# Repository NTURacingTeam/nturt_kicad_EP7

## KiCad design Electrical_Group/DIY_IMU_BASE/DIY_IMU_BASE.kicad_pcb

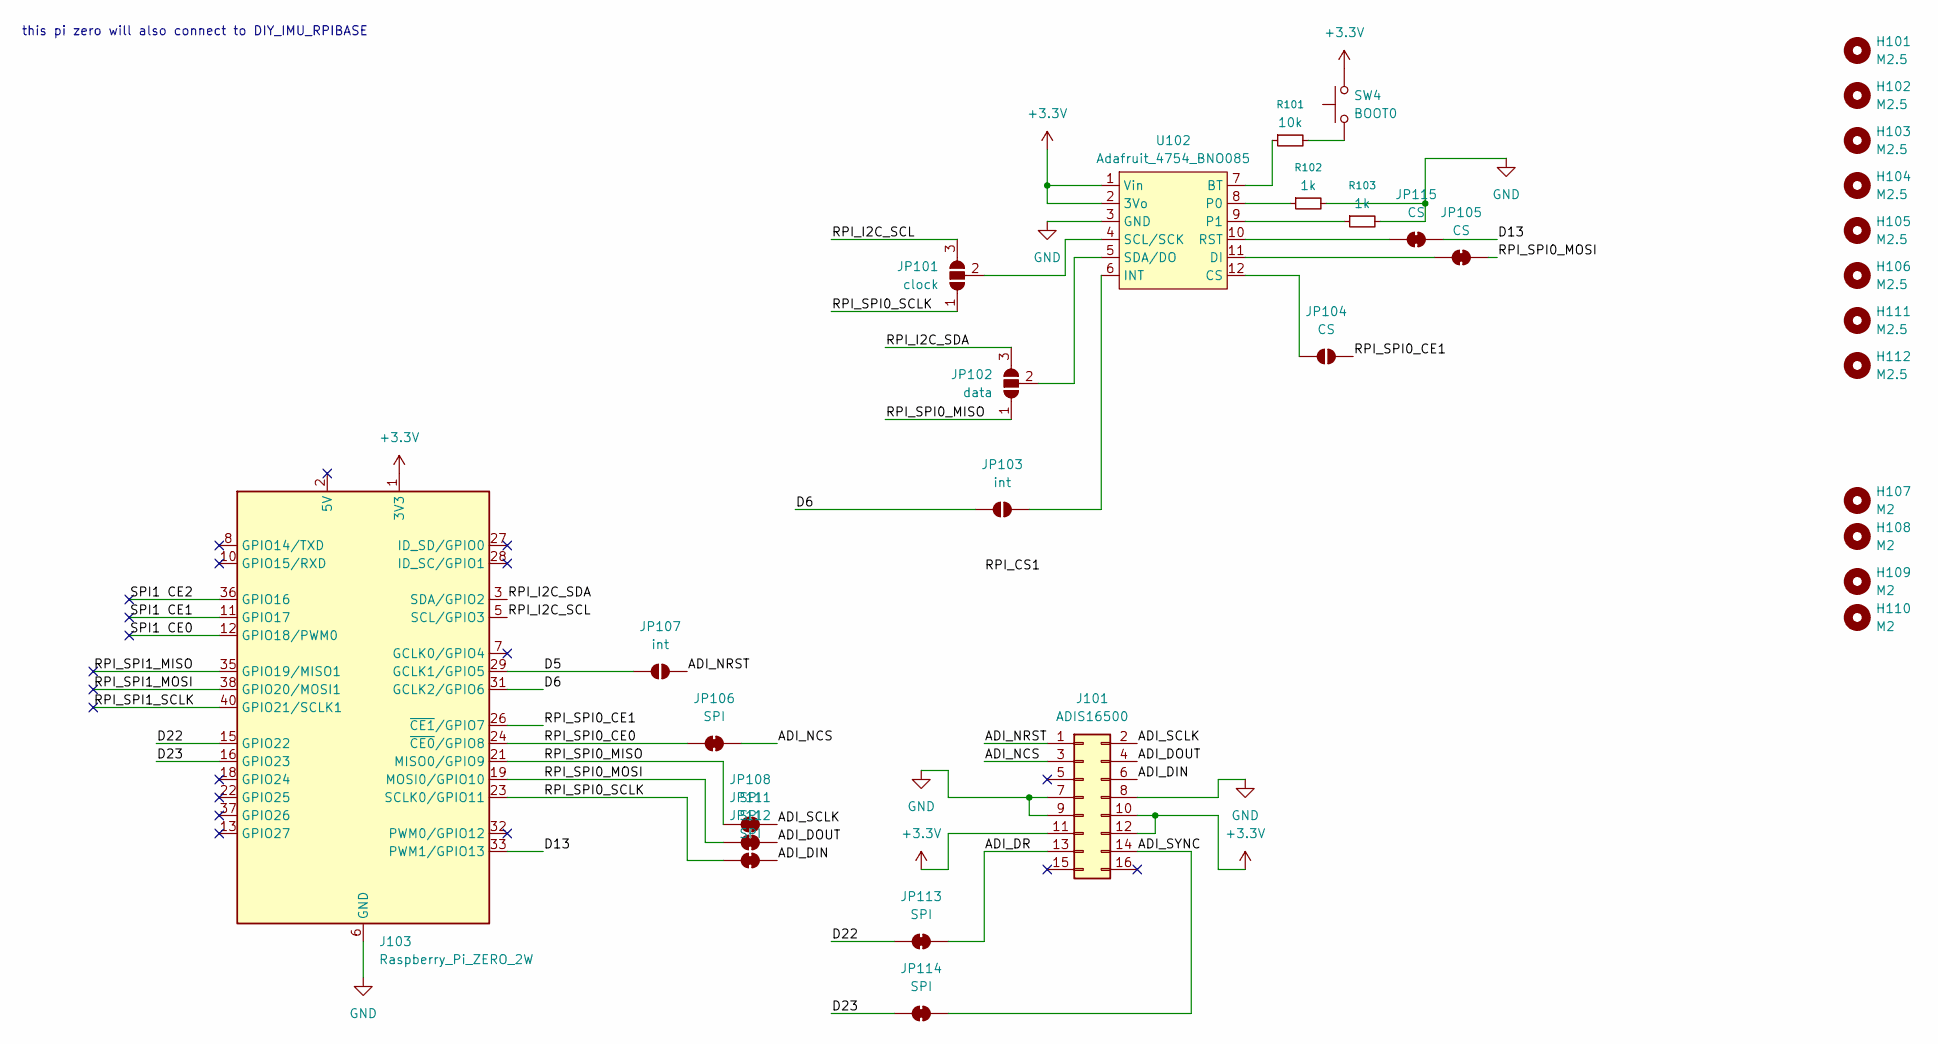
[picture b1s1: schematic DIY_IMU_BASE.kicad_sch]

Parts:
H101, H102, H103, H104, H105, H106, H111, H112: M2.5; MountingHole_2.5mm
H107, H108, H109, H110: M2; MountingHole_2.2mm_M2
J101: ADIS16500; PinHeader_2x08_P2.00mm_Vertical_SMD
J103: Raspberry_Pi_ZERO_2W; PinHeader_2x20_P2.54mm_Vertical
JP101: clock; SolderJumper-3_P1.3mm_Open_RoundedPad1.0x1.5mm
JP102: data; SolderJumper-3_P1.3mm_Open_RoundedPad1.0x1.5mm
JP103, JP107: int; SolderJumper-2_P1.3mm_Open_RoundedPad1.0x1.5mm
JP104: CS; SolderJumper-2_P1.3mm_Open_RoundedPad1.0x1.5mm
JP105, JP115: CS; SolderJumper-2_P1.3mm_Bridged_RoundedPad1.0x1.5mm
JP106, JP108, JP111, JP112, JP113, JP114: SPI; SolderJumper-2_P1.3mm_Bridged_RoundedPad1.0x1.5mm
R101: 10k; R_0805_2012Metric_Pad1.20x1.40mm_HandSolder
R102, R103: 1k; R_0805_2012Metric_Pad1.20x1.40mm_HandSolder
SW4: BOOT0; SW_Tactile_SPST_NO_Straight_CK_PTS636Sx25SMTRLFS
U102: Adafruit_4754_BNO085

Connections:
+3.3V: J101.10, J101.11, J101.12, J103.1 (3V3), J103.17 (3V3), SW4.2, U102.1 (Vin), U102.2 (3Vo)
/ADI_DIN: J101.6, JP112.2 (B)
/ADI_DOUT: J101.4, JP111.2 (B)
/ADI_DR: J101.13, JP113.2 (B)
/ADI_NCS: J101.3, JP106.2 (B)
/ADI_NRST: J101.1, JP107.2 (B)
/ADI_SCLK: J101.2, JP108.2 (B)
/ADI_SYNC: J101.14, JP114.2 (B)
/D5: J103.29 (GCLK1/GPIO5), JP107.1 (A)
/D6: J103.31 (GCLK2/GPIO6), JP103.1 (A)
/D13: J103.33 (PWM1/GPIO13), JP115.2 (B)
/D22: J103.15 (GPIO22), JP113.1 (A)
/D23: J103.16 (GPIO23), JP114.1 (A)
/RPI_I2C_SCL: J103.5 (SCL/GPIO3), JP101.3 (B)
/RPI_I2C_SDA: J103.3 (SDA/GPIO2), JP102.3 (B)
/RPI_SPI0_CE0: J103.24 (~CE0/GPIO8), JP106.1 (A)
/RPI_SPI0_CE1: J103.26 (~CE1/GPIO7), JP104.2 (B)
/RPI_SPI0_MISO: J103.21 (MISO0/GPIO9), JP102.1 (A), JP108.1 (A)
/RPI_SPI0_MOSI: J103.19 (MOSI0/GPIO10), JP105.2 (B), JP111.1 (A)
/RPI_SPI0_SCLK: J103.23 (SCLK0/GPIO11), JP101.1 (A), JP112.1 (A)
/RPI_SPI1_MISO: J103.35 (GPIO19/MISO1)
/RPI_SPI1_MOSI: J103.38 (GPIO20/MOSI1)
/RPI_SPI1_SCLK: J103.40 (GPIO21/SCLK1)
/SPI1 CE0: J103.12 (GPIO18/PWM0)
/SPI1 CE1: J103.11 (GPIO17)
/SPI1 CE2: J103.36 (GPIO16)
GND: J101.7, J101.8, J101.9, J103.6 (GND), J103.9 (GND), J103.14 (GND), J103.20 (GND), J103.25 (GND), J103.30 (GND), J103.34 (GND), J103.39 (GND), R102.2, R103.2, U102.3 (GND)
unnamed: JP101.2 (C), U102.4 (SCL/SCK)
unnamed: JP102.2 (C), U102.5 (SDA/DO)
unnamed: JP103.2 (B), U102.6 (INT)
unnamed: JP104.1 (A), U102.12 (CS)
unnamed: JP105.1 (A), U102.11 (DI)
unnamed: JP115.1 (A), U102.10 (RST)
unnamed: R101.2, SW4.1
unnamed: R101.1, U102.7 (BT)
unnamed: R102.1, U102.8 (P0)
unnamed: R103.1, U102.9 (P1)

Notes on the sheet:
this pi zero will also connect to DIY_IMU_RPIBASE

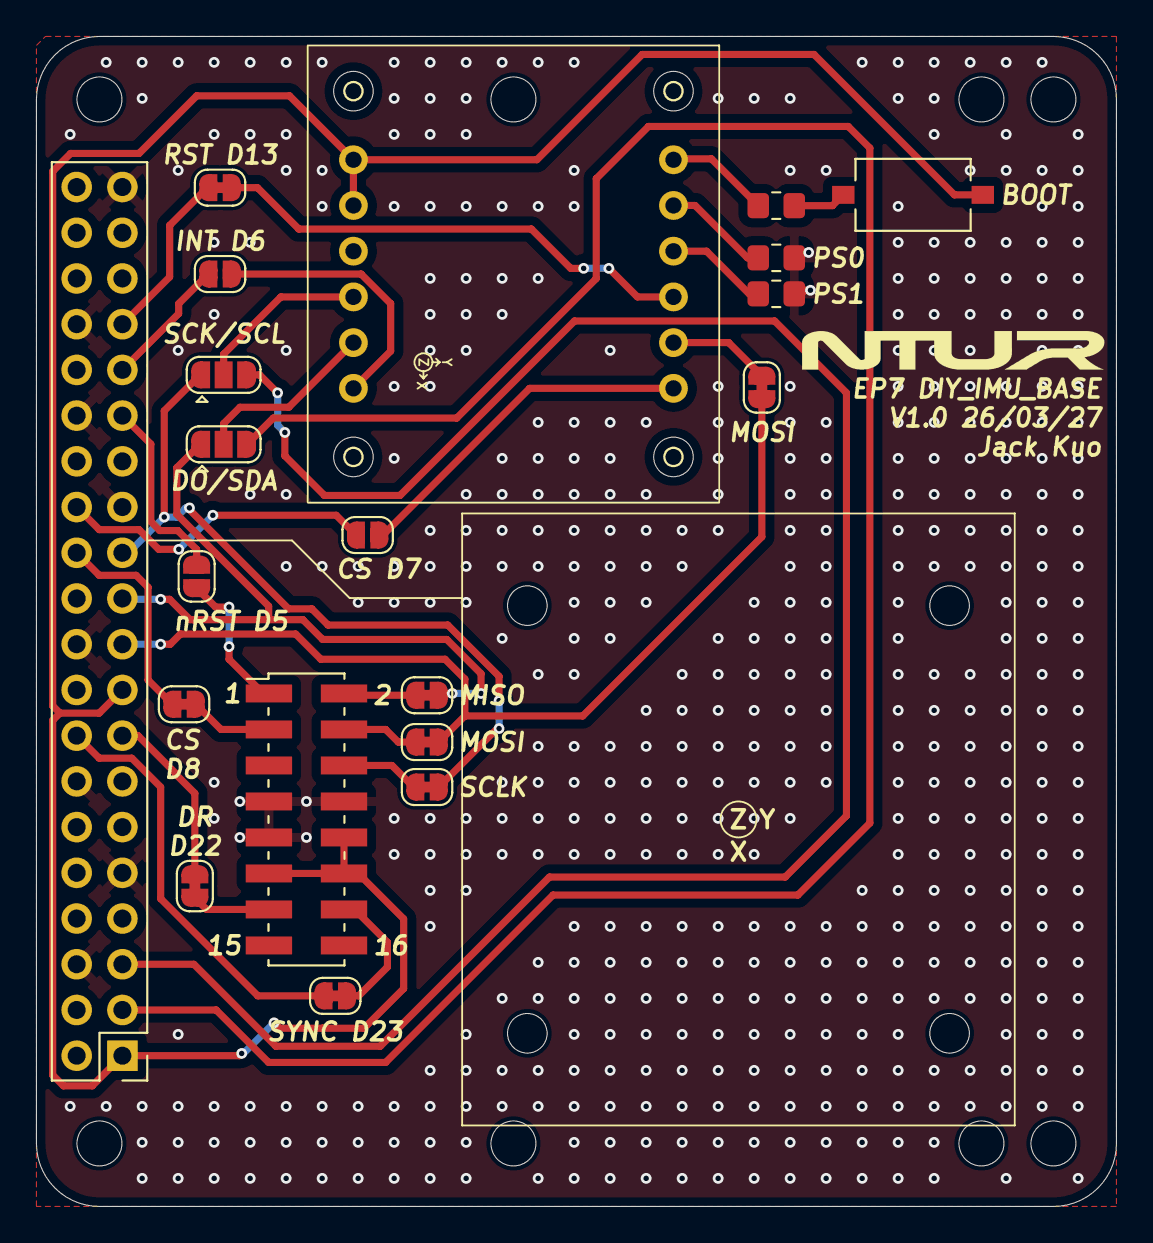
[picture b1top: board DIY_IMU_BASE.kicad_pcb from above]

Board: 2 copper layers, 60.0 x 65.0 mm, 32 parts (0 on the bottom side), 31 nets.

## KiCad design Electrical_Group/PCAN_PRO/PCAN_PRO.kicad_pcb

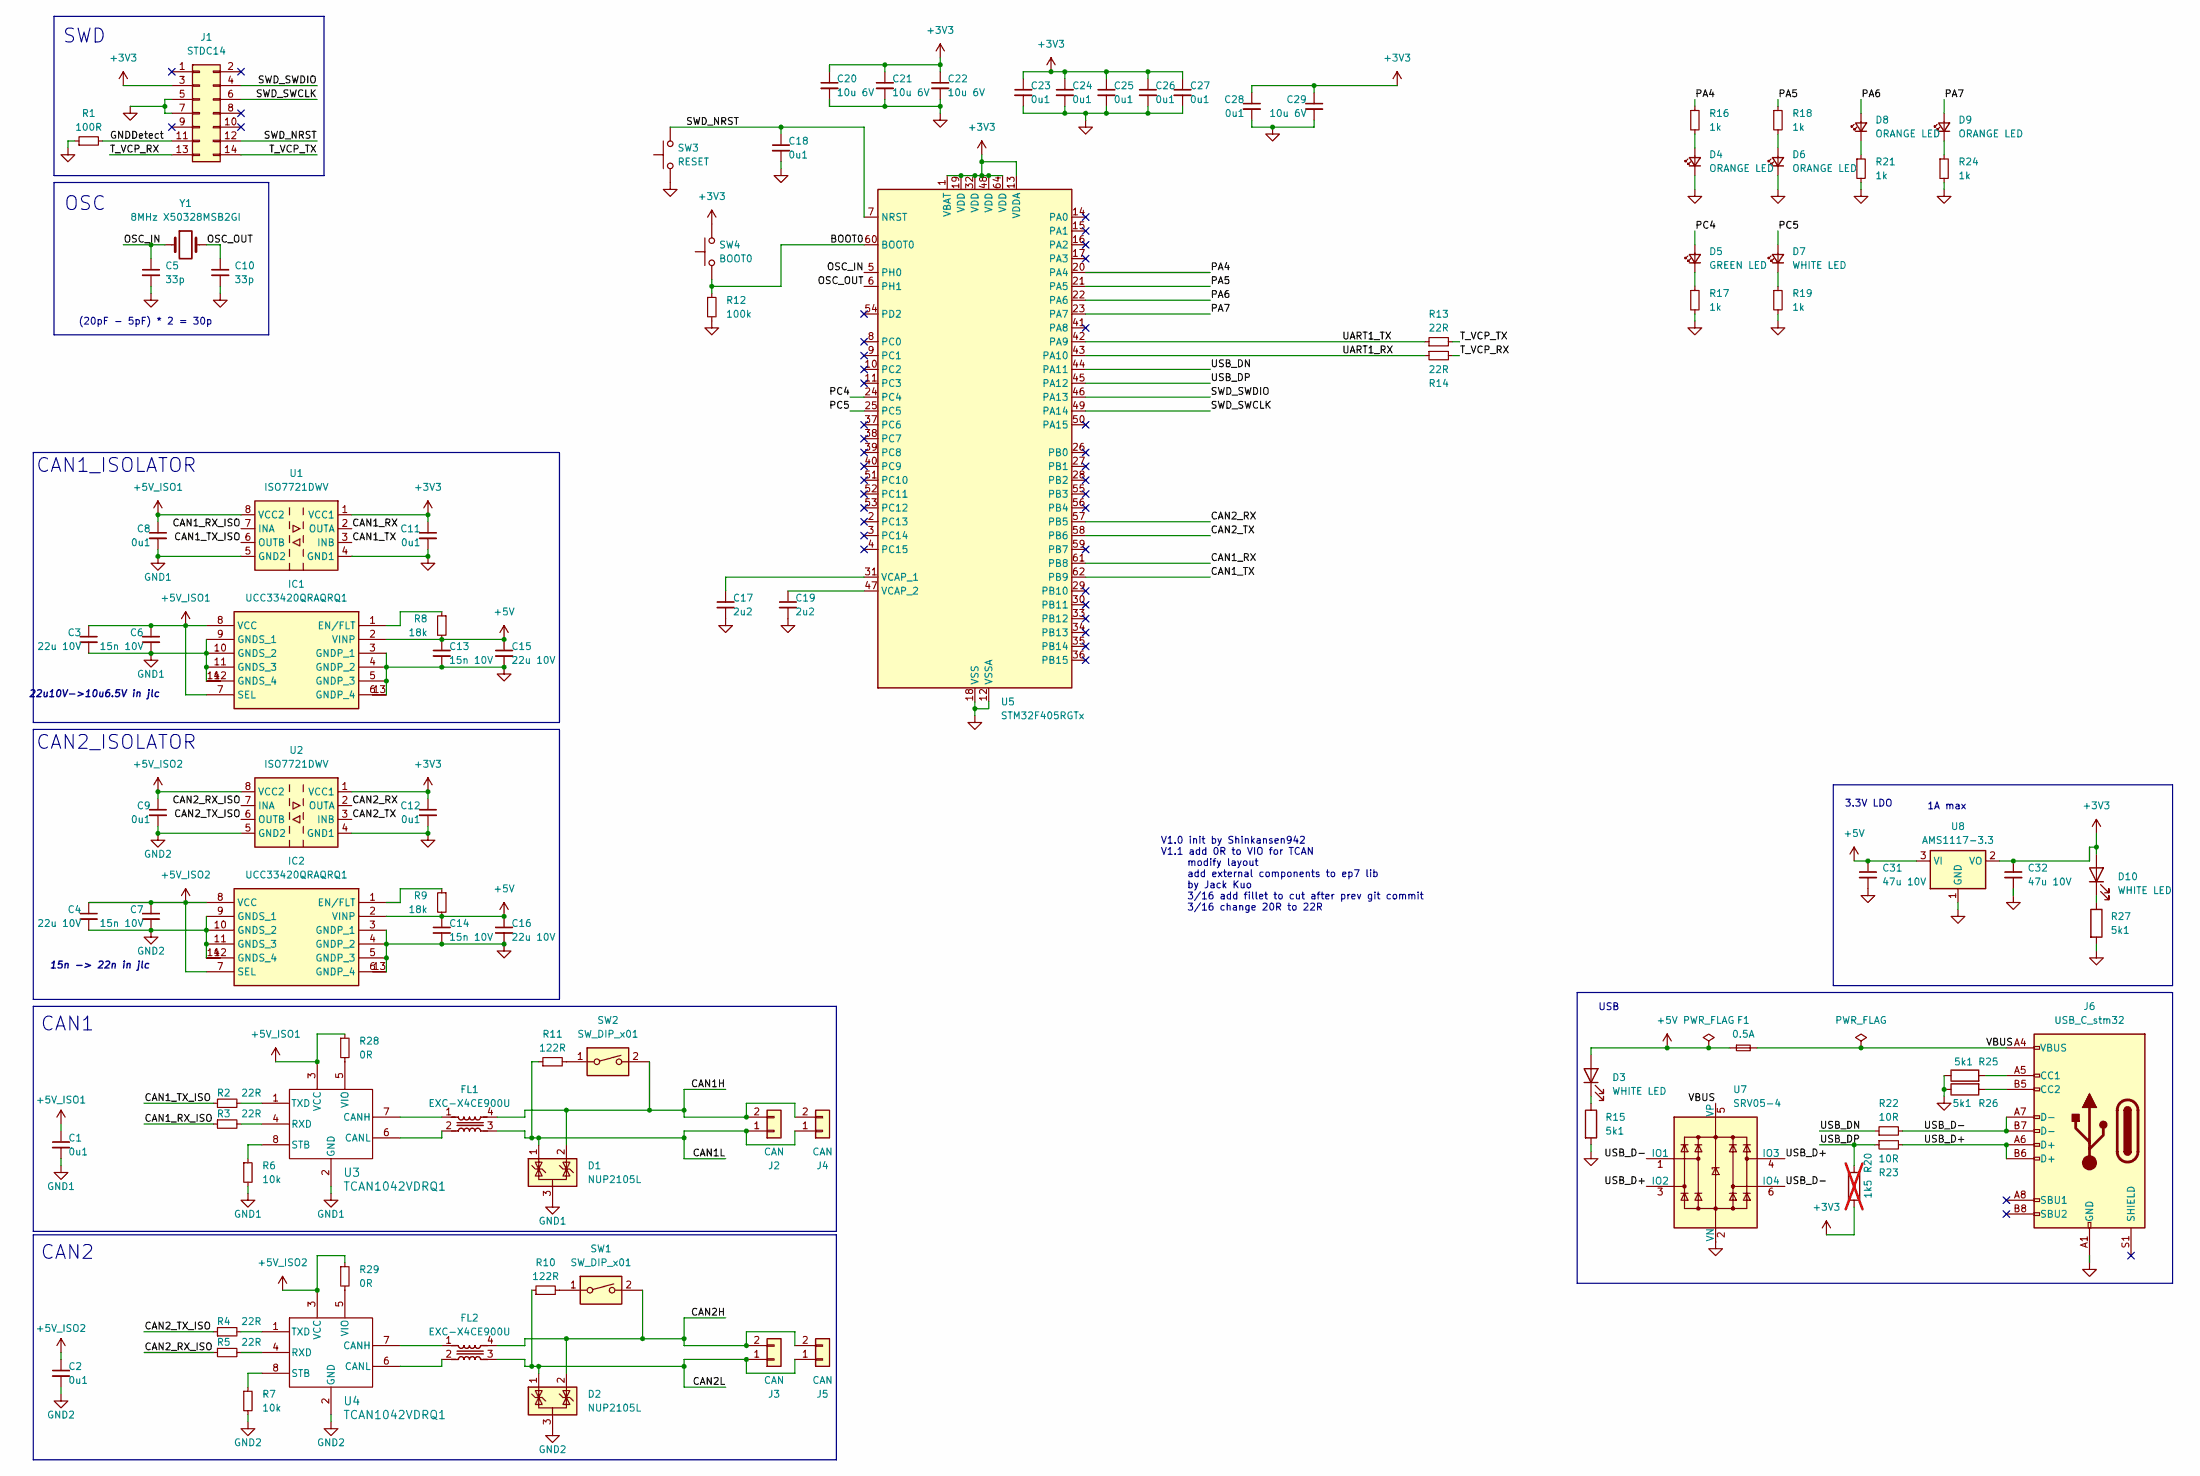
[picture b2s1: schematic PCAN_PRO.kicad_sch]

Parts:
C1, C2, C8, C9, C11, C12, C18, C23, C24, C25, C26, C27, C28: 0u1; C_0402_1005Metric
C3, C4, C15, C16: 22u 10V; C_0402_1005Metric
C5, C10: 33p; C_0402_1005Metric
C6, C7, C13, C14: 15n 10V; C_0402_1005Metric
C17, C19: 2u2; C_0402_1005Metric
C20, C21, C22, C29: 10u 6V; C_0402_1005Metric
C31, C32: 47u 10V; C_1206_3216Metric
D1, D2: NUP2105L; SOT-23
D3, D7, D10: WHITE LED; LED_0603_1608Metric
D4, D6, D8, D9: ORANGE LED; LED_0603_1608Metric
D5: GREEN LED; LED_0603_1608Metric
F1: 0.5A; Fuse_1206_3216Metric
FL1, FL2: EXC-X4CE900U; EXCX4CE900U; Mouser Part Number 667-EXC-X4CE900U
IC1, IC2: UCC33420QRAQRQ1; UCC33020; Mouser Part Number 595-UCC33420QRAQRQ1
J1: STDC14; box_header_14P_pitch1.27
J2, J3, J4, J5: CAN; JST_XH_B2B-XH-A_1x02_P2.50mm_Vertical
J6: USB_C_stm32; USB_C_Receptacle_GCT_USB4105-xx-A_16P_TopMnt_Horizontal
R1: 100R; R_0402_1005Metric
R2, R3, R4, R5, R13, R14: 22R; R_0402_1005Metric
R6, R7: 10k; R_0402_1005Metric
R8, R9: 18k; R_0402_1005Metric
R10, R11: 122R; R_0805_2012Metric
R12: 100k; R_0402_1005Metric
R15, R25, R26, R27: 5k1; R_0402_1005Metric
R16, R17, R18, R19, R21, R24: 1k; R_0402_1005Metric
R20: 1k5; R_0402_1005Metric; not fitted
R22, R23: 10R; R_0402_1005Metric
R28, R29: 0R; R_0402_1005Metric
SW1, SW2: SW_DIP_x01; SW_DIP_SPSTx01_Slide_9.78x4.72mm_W7.62mm_P2.54mm
SW3: RESET; SW_Tactile_SPST_NO_Straight_CK_PTS636Sx25SMTRLFS
SW4: BOOT0; SW_Tactile_SPST_NO_Straight_CK_PTS636Sx25SMTRLFS
U1, U2: ISO7721DWV; SOIC-8_7.5x5.85mm_P1.27mm
U3, U4: TCAN1042VDRQ1; SOIC-8_3.9x4.9mm_P1.27mm
U5: STM32F405RGTx; LQFP-64_10x10mm_P0.5mm
U7: SRV05-4; SOT-23-6
U8: AMS1117-3.3; SOT-223-3_TabPin2
Y1: 8MHz X50328MSB2GI; Crystal_SMD_5032-2Pin_5.0x3.2mm

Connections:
+3V3: C11.1, C12.1, C20.1, C21.1, C22.1, C23.1, C24.1, C25.1, C26.1, C27.1, C28.1, C29.1, C32.1, D10.2 (A), J1.3, R20.1, SW4.2, U1.1 (VCC1), U2.1 (VCC1), U5.1 (VBAT), U5.13 (VDDA), U5.19 (VDD), U5.32 (VDD), U5.48 (VDD), U5.64 (VDD), U8.2 (VO)
+5V: C13.1, C14.1, C15.1, C16.1, C31.1, D3.2 (A), F1.1, IC1.2 (VINP), IC2.2 (VINP), R8.2, R9.2, U8.3 (VI)
+5V_ISO1: C1.1, C3.1, C6.1, C8.1, IC1.7 (SEL), IC1.8 (VCC), R28.1, U1.8 (VCC2), U3.3 (VCC)
+5V_ISO2: C2.1, C4.1, C7.1, C9.1, IC2.7 (SEL), IC2.8 (VCC), R29.1, U2.8 (VCC2), U4.3 (VCC)
/BOOT0: R12.1, SW4.1, U5.60 (BOOT0)
/CAN1H: D1.2 (K), FL1.4, J2.2, J4.2, SW2.2
/CAN1L: D1.1 (K), FL1.3, J2.1, J4.1, R11.1
/CAN1_RX: U1.2 (OUTA), U5.61 (PB8)
/CAN1_RX_ISO: R3.1, U1.7 (INA)
/CAN1_TX: U1.3 (INB), U5.62 (PB9)
/CAN1_TX_ISO: R2.1, U1.6 (OUTB)
/CAN2H: D2.2 (K), FL2.4, J3.2, J5.2, SW1.2
/CAN2L: D2.1 (K), FL2.3, J3.1, J5.1, R10.1
/CAN2_RX: U2.2 (OUTA), U5.57 (PB5)
/CAN2_RX_ISO: R5.1, U2.7 (INA)
/CAN2_TX: U2.3 (INB), U5.58 (PB6)
/CAN2_TX_ISO: R4.1, U2.6 (OUTB)
/GNDDetect: J1.11, R1.2
/OSC_IN: C5.1, U5.5 (PH0), Y1.1
/OSC_OUT: C10.1, U5.6 (PH1), Y1.2
/PA4: R16.1, U5.20 (PA4)
/PA5: R18.1, U5.21 (PA5)
/PA6: D8.2 (A), U5.22 (PA6)
/PA7: D9.2 (A), U5.23 (PA7)
/PC4: D5.2 (A), U5.24 (PC4)
/PC5: D7.2 (A), U5.25 (PC5)
/SWD_NRST: C18.1, J1.12, SW3.2, U5.7 (NRST)
/SWD_SWCLK: J1.6, U5.49 (PA14)
/SWD_SWDIO: J1.4, U5.46 (PA13)
/T_VCP_RX: J1.13, R14.2
/T_VCP_TX: J1.14, R13.2
/UART1_RX: R14.1, U5.43 (PA10)
/UART1_TX: R13.1, U5.42 (PA9)
/USB_D+: J6.A6 (D+), J6.B6 (D+), R23.2, U7.3 (IO2), U7.4 (IO3)
/USB_D-: J6.A7 (D-), J6.B7 (D-), R22.2, U7.1 (IO1), U7.6 (IO4)
/USB_DN: R22.1, U5.44 (PA11)
/USB_DP: R20.2, R23.1, U5.45 (PA12)
/VBUS: F1.2, J6.A4 (VBUS), J6.A9 (VBUS), J6.B4 (VBUS), J6.B9 (VBUS), U7.5 (VP)
GND: C5.2, C10.2, C11.2, C12.2, C13.2, C14.2, C15.2, C16.2, C17.2, C18.2, C19.2, C20.2, C21.2, C22.2, C23.2, C24.2, C25.2, C26.2, C27.2, C28.2, C29.2, C31.2, C32.2, D4.1 (K), D6.1 (K), IC1.3 (GNDP_1), IC1.4 (GNDP_2), IC1.5 (GNDP_3), IC1.6 (GNDP_4), IC1.13, IC2.3 (GNDP_1), IC2.4 (GNDP_2), IC2.5 (GNDP_3), IC2.6 (GNDP_4), IC2.13, J1.5, J1.7, J6.A1 (GND), J6.A12 (GND), J6.B1 (GND), J6.B12 (GND), R1.1, R12.2, R15.2, R17.2, R19.2, R21.2, R24.2, R25.1, R26.1, R27.2, SW3.1, U1.4 (GND1), U2.4 (GND1), U5.12 (VSSA), U5.18 (VSS), U5.63 (VSS), U7.2 (VN), U8.1 (GND)
GND1: C1.2, C3.2, C6.2, C8.2, D1.3 (A), IC1.9 (GNDS_1), IC1.10 (GNDS_2), IC1.11 (GNDS_3), IC1.12 (GNDS_4), IC1.14, R6.2, U1.5 (GND2), U3.2 (GND)
GND2: C2.2, C4.2, C7.2, C9.2, D2.3 (A), IC2.9 (GNDS_1), IC2.10 (GNDS_2), IC2.11 (GNDS_3), IC2.12 (GNDS_4), IC2.14, R7.2, U2.5 (GND2), U4.2 (GND)
unnamed: D3.1 (K), R15.1
unnamed: D4.2 (A), R16.2
unnamed: D5.1 (K), R17.1
unnamed: D6.2 (A), R18.2
unnamed: D7.1 (K), R19.1
unnamed: D8.1 (K), R21.1
unnamed: D9.1 (K), R24.1
unnamed: D10.1 (K), R27.1
unnamed: IC1.1 (EN/FLT), R8.1
unnamed: IC2.1 (EN/FLT), R9.1
unnamed: J6.A5 (CC1), R25.2
unnamed: J6.B5 (CC2), R26.2
unnamed: R10.2, SW1.1
unnamed: R11.2, SW2.1
unnamed: FL1.1, U3.7 (CANH)
unnamed: FL1.2, U3.6 (CANL)
unnamed: R3.2, U3.4 (RXD)
unnamed: R6.1, U3.8 (STB)
unnamed: R2.2, U3.1 (TXD)
unnamed: R28.2, U3.5 (VIO)
unnamed: FL2.1, U4.7 (CANH)
unnamed: FL2.2, U4.6 (CANL)
unnamed: R5.2, U4.4 (RXD)
unnamed: R7.1, U4.8 (STB)
unnamed: R4.2, U4.1 (TXD)
unnamed: R29.2, U4.5 (VIO)
unnamed: C17.1, U5.31 (VCAP_1)
unnamed: C19.1, U5.47 (VCAP_2)

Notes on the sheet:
SWD
CAN1
CAN1_ISOLATOR
1A max
3.3V LDO
(20pF - 5pF) * 2 = 30p
USB
CAN2
V1.0 init by Shinkansen942 V1.1 add 0R to VIO for TCAN modify layout add external components to ep7 lib by Jack Kuo 3/16 add fillet to cut after prev git commit 3/16 change 20R to 22R
CAN2_ISOLATOR
OSC
22u10V->10u6.5V in jlc
15n -> 22n in jlc

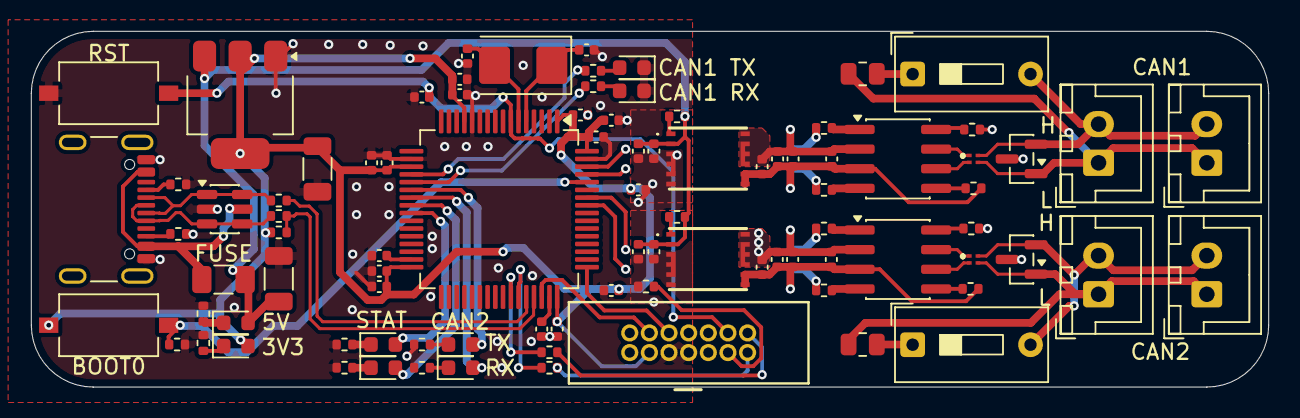
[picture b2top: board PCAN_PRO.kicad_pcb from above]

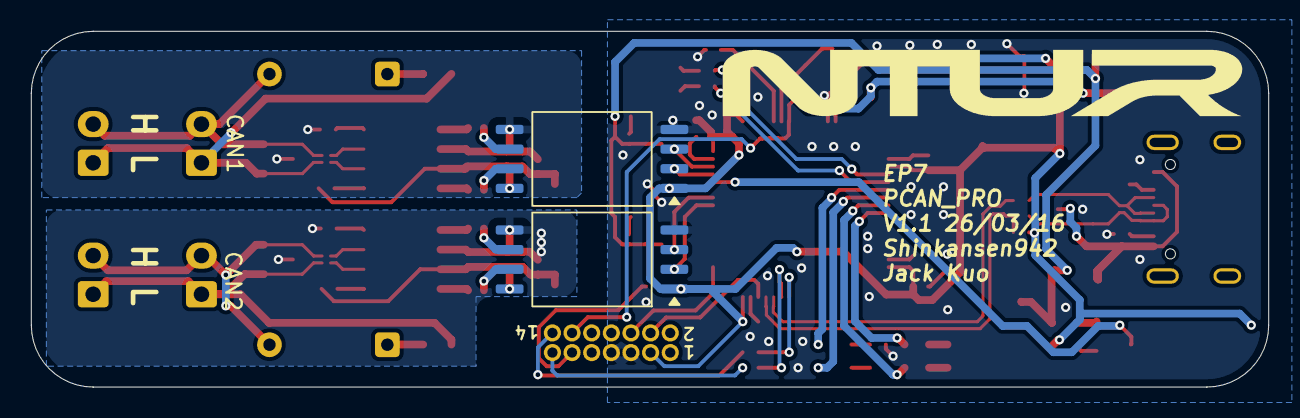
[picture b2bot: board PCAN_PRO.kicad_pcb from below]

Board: 2 copper layers, 80.0 x 23.0 mm, 93 parts (2 on the bottom side), 69 nets.

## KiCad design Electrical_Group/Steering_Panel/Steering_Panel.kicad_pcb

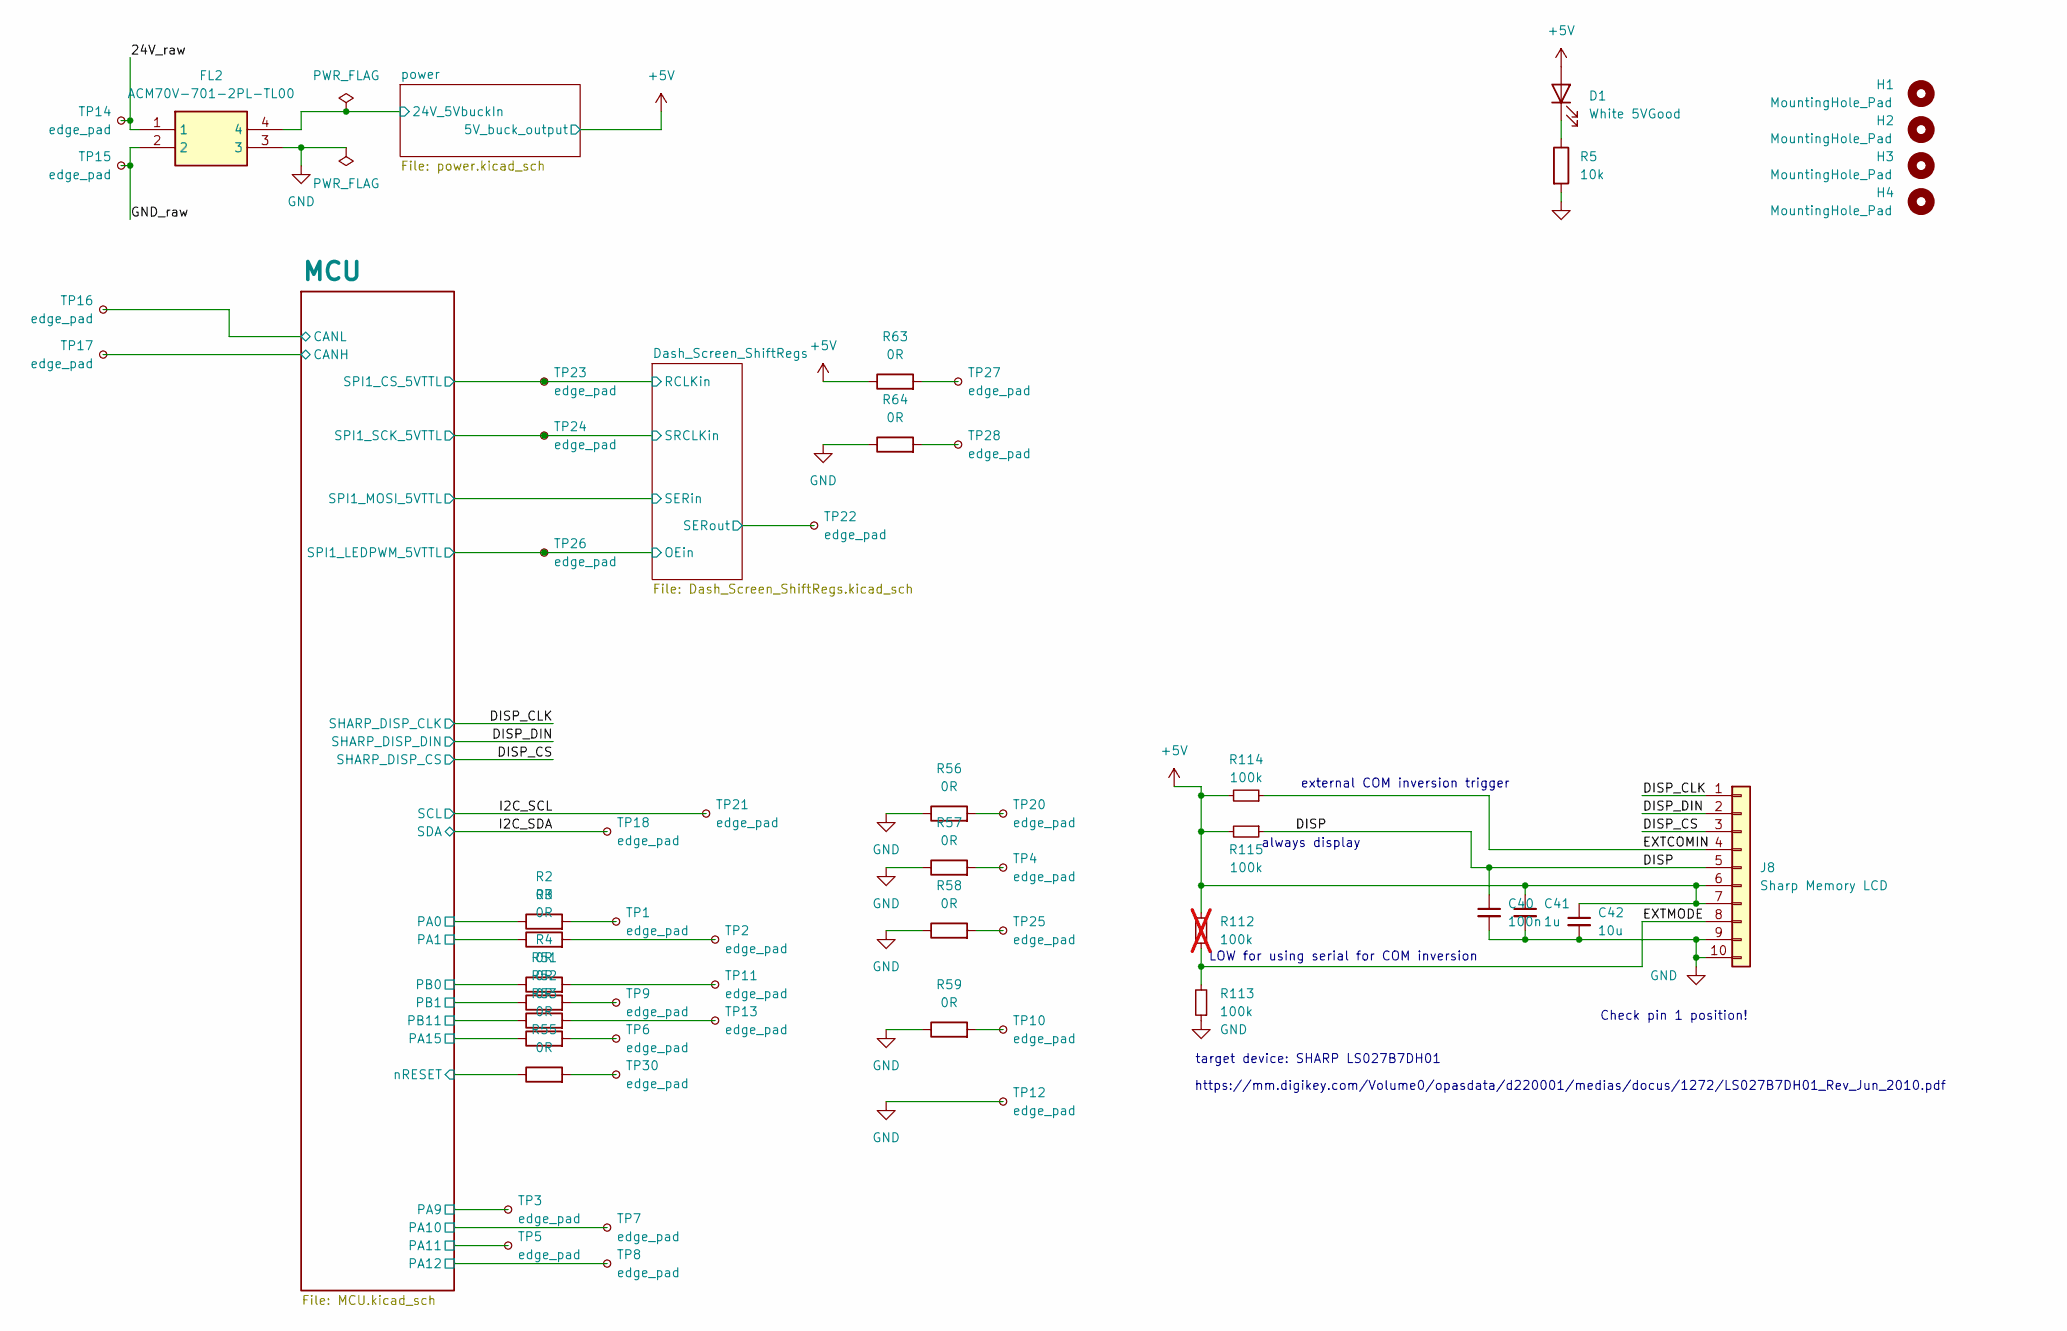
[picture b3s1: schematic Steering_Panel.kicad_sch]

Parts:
C40: 100n; C_0603_1608Metric
C41: 1u; C_0603_1608Metric
C42: 10u; C_0603_1608Metric
D1: White 5VGood; LED_0603_1608Metric
FL2: ACM70V-701-2PL-TL00; Common_Mode_Choke_4A_ACM70V7012PLTL00; Mouser Part Number 810-ACM70V7012PLTL00
H1, H2, H3, H4: MountingHole_Pad; MountingHole_3.2mm_M3
J8: Sharp Memory LCD; TE_1-1734839-0_1x10-1MP_P0.5mm_Horizontal
R2, R3, R4, R51, R52, R53, R55, R56, R57, R58, R59, R63, R64: 0R; R_0603_1608Metric
R5: 10k; R_0603_1608Metric
R112: 100k; R_0603_1608Metric; not fitted
R113, R114, R115: 100k; R_0603_1608Metric
TP1, TP2, TP3, TP4, TP5, TP6, TP7, TP8, TP9, TP10, TP11, TP12, TP13, TP14, TP15, TP16, TP17, TP18, TP20, TP21, TP22, TP23, TP24, TP25, TP26, TP27, TP28, TP30: edge_pad; edge_pad_1.4mm_0.7mm

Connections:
+5V: C41.1, C42.1, D1.2 (A), J8.6, J8.7, R63.1, R112.2, R114.2, R115.2; also elsewhere on the board
/24V_raw: FL2.1, TP14.1
/DISP: C40.1, J8.5, R115.1
/DISP_CLK: J8.1; also elsewhere on the board
/DISP_CS: J8.3; also elsewhere on the board
/DISP_DIN: J8.2; also elsewhere on the board
/Dash_Screen_ShiftRegs/LEDend5: TP22.1; also elsewhere on the board
/Dash_Screen_ShiftRegs/OE: TP26.1; also elsewhere on the board
/Dash_Screen_ShiftRegs/RCLK: TP23.1; also elsewhere on the board
/Dash_Screen_ShiftRegs/SRCLK: TP24.1; also elsewhere on the board
/EXTCOMIN: J8.4, R114.1
/EXTMODE: J8.8, R112.1, R113.2
/GND_raw: FL2.2, TP15.1
/I2C_SCL: TP21.1; also elsewhere on the board
/I2C_SDA: TP18.1; also elsewhere on the board
/MCU/CANH: TP17.1; also elsewhere on the board
/MCU/CANL: TP16.1; also elsewhere on the board
/MCU/NRST: R55.1; also elsewhere on the board
/MCU/PA0: R2.1; also elsewhere on the board
/MCU/PA1: R3.1; also elsewhere on the board
/MCU/PA9: TP3.1; also elsewhere on the board
/MCU/PA10: TP7.1; also elsewhere on the board
/MCU/PA11: TP5.1; also elsewhere on the board
/MCU/PA12: TP8.1; also elsewhere on the board
/MCU/PA15: R53.1; also elsewhere on the board
/MCU/PB0: R4.1; also elsewhere on the board
/MCU/PB1: R51.1; also elsewhere on the board
/MCU/PB11: R52.1; also elsewhere on the board
/power/24V_5VbuckIn: FL2.4; also elsewhere on the board
GND: C40.2, C41.2, C42.2, FL2.3, J8.9, J8.10, R5.2, R56.1, R57.1, R58.1, R59.1, R64.1, R113.1, TP12.1; also elsewhere on the board
unnamed: D1.1 (K), R5.1
unnamed: R2.2, TP1.1
unnamed: R3.2, TP2.1
unnamed: R4.2, TP11.1
unnamed: R51.2, TP9.1
unnamed: R52.2, TP13.1
unnamed: R53.2, TP6.1
unnamed: R55.2, TP30.1
unnamed: R56.2, TP20.1
unnamed: R57.2, TP4.1
unnamed: R58.2, TP25.1
unnamed: R59.2, TP10.1
unnamed: R63.2, TP27.1
unnamed: R64.2, TP28.1

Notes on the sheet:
Check pin 1 position!
target device: SHARP LS027B7DH01
LOW for using serial for COM inversion
external COM inversion trigger
always display
https://mm.digikey.com/Volume0/opasdata/d220001/medias/docus/1272/LS027B7DH01_Rev_Jun_2010.pdf
